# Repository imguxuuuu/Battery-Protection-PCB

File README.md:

# 🔋 Li-Ion Battery Protection PCB

> A compact single-cell (3.7 V) Li-Ion battery protection and voltage monitoring PCB designed using **KiCad 9**.

This project demonstrates the complete PCB design workflow, including schematic capture, PCB layout, routing, copper pour, design rule verification, Gerber generation, and manufacturing documentation.

---

# 📸 Project Banner

---

# 📖 Project Overview

This PCB provides a simple yet reliable protection and monitoring solution for a single-cell Li-Ion battery.

The design includes:

- Reverse-current protection
- Overcurrent protection
- Battery voltage sensing
- Power indication
- Test points
- Manufacturing-ready outputs

The project was developed to demonstrate practical PCB design skills and follows good engineering documentation practices suitable for a hardware portfolio.

---

# ✨ Features

- ✅ Reverse current protection using **1N5819 Schottky diode**
- ✅ 500 mA resettable Polyfuse
- ✅ Battery voltage divider for MCU ADC
- ✅ 100 nF analog filter capacitor
- ✅ Green power indicator LED
- ✅ BAT_ADC and GND test points
- ✅ 90 mm × 40 mm PCB
- ✅ Ground copper pour
- ✅ Passed KiCad DRC (0 Errors)
- ✅ Manufacturing-ready Gerber files

---

# 📊 PCB Specifications

| Parameter | Value |
|-----------|--------|
| Board Size | 90 mm × 40 mm |
| Layers | 2 |
| Copper Weight | 1 oz |
| Input Voltage | 3.0–4.2 V DC |
| Nominal Voltage | 3.7 V Li-Ion |
| Design Software | KiCad 9 |
| DRC Status | Passed (0 Errors) |

---

# ⚡ Circuit Overview

The battery output first passes through a **500 mA resettable Polyfuse**, providing overcurrent protection.

The protected voltage is then routed through a **1N5819 Schottky diode**, preventing reverse current flow.

The output powers:

- Output connector
- Power indicator LED
- Battery voltage monitoring circuit

Battery voltage is measured using a **100 kΩ / 100 kΩ resistor divider** followed by a **100 nF RC filter**, providing a stable analog voltage for a microcontroller ADC.

---

# 🔄 Functional Block Diagram

```text
Battery
   │
   ▼
PTC Fuse
   │
   ▼
Schottky Diode
   │
   ▼
BAT_OUT
 ├──► LED Indicator
 └──► ADC Voltage Divider
```

---

# 🖼️ Project Images

## Schematic

---

## PCB Top View

---

## 3D PCB View

---

## Gerber Verification

---

# 📁 Repository Structure

```text
docs/
gerbers/
images/
pcb/
references/
releases/
simulation/
```

---

# 📋 Bill of Materials

See **BOM.csv**

---

# ✔ Verification

- ERC Completed
- DRC Passed (0 Errors)
- Copper Pour Verified
- Gerbers Verified
- Drill Files Generated
- Fabrication Package Prepared

---

# 🛠 Software Used

- KiCad 9
- KiCad Gerber Viewer
- LTspice XVII
- Git
- GitHub

---

# 🚀 Future Improvements

- DW01A Battery Protection IC
- USB Type-C Charging Circuit
- Reverse Polarity MOSFET Protection
- Battery Fuel Gauge
- JST Battery Connector
- Current Sense Amplifier
- TVS Surge Protection
- Mounting Holes

---

# 📚 Documentation

- Project Report
- Project Specification
- Design Decisions
- Manufacturing Notes
- Component Datasheets
- PCB Design Checklist

---

# 📄 License

This project is licensed under the **MIT License**.

See the `LICENSE` file for details.

---

## ⭐ Acknowledgements

Designed using **KiCad 9** as part of a hardware engineering portfolio project demonstrating PCB design, documentation, and manufacturing preparation.

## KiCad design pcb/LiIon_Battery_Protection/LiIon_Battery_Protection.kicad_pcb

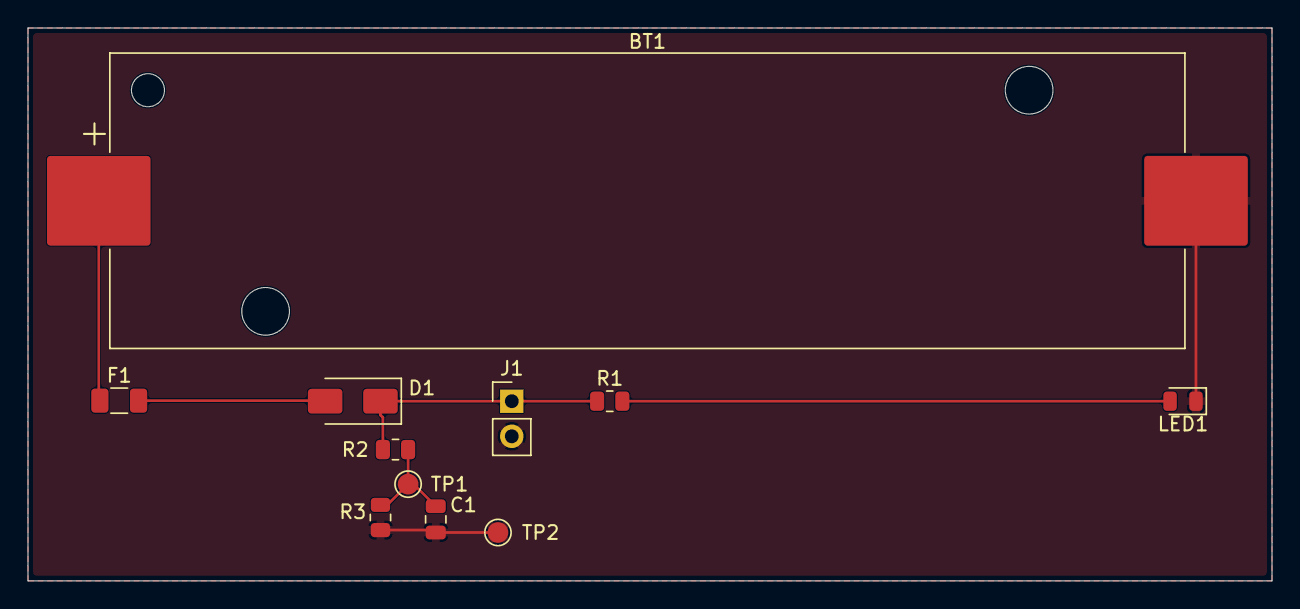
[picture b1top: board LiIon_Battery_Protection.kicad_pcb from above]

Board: 2 copper layers, 90.0 x 40.0 mm, 11 parts (0 on the bottom side), 6 nets.

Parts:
BT1: Li-Ion 3.7V; BatteryHolder_Keystone_1042_1x18650
C1: 100nF; C_0805_2012Metric
D1: 1N5819; D_SMA
F1: 500mA PTC; Fuse_1206_3216Metric
J1: BAT_OUT; PinHeader_1x02_P2.54mm_Vertical
LED1: Green; LED_0805_2012Metric
R1: 330; R_0805_2012Metric
R2, R3: 100k; R_0805_2012Metric
TP1: BAT_ADC; TestPoint_Pad_D1.5mm
TP2: GND_TEST; TestPoint_Pad_D1.5mm

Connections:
/BAT_PROTECTED: D1.1 (K), J1.1, R1.1, R2.1
/BAT_RAW: BT1.1 (+), F1.1
GND: BT1.2 (-), C1.2, J1.2, LED1.1 (K), R3.2, TP2.1 (1_1)
unnamed: C1.1, R2.2, R3.1, TP1.1 (1_1)
unnamed: D1.2 (A), F1.2
unnamed: LED1.2 (A), R1.2

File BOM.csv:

Reference,Quantity,Value,Footprint,Description
BT1,1,18650 Holder,Battery Holder,Single Cell Holder
F1,1,500mA PTC,1812 Resettable Fuse,Polyfuse
D1,1,1N5819,SMA Schottky,Reverse Polarity Protection
R1,1,330Ω,0805,LED Current Limiting
R2,1,100kΩ,0805,Voltage Divider Upper
R3,1,100kΩ,0805,Voltage Divider Lower
C1,1,100nF,0805,ADC Filter Capacitor
LED1,1,Green LED,0805,Power Indicator
J1,1,2-Pin Terminal,Terminal Block,Power Output
TP1,1,Test Point,1.5mm Pad,Battery ADC
TP2,1,Test Point,1.5mm Pad,Ground Test

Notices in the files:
README.md:
License: MIT
